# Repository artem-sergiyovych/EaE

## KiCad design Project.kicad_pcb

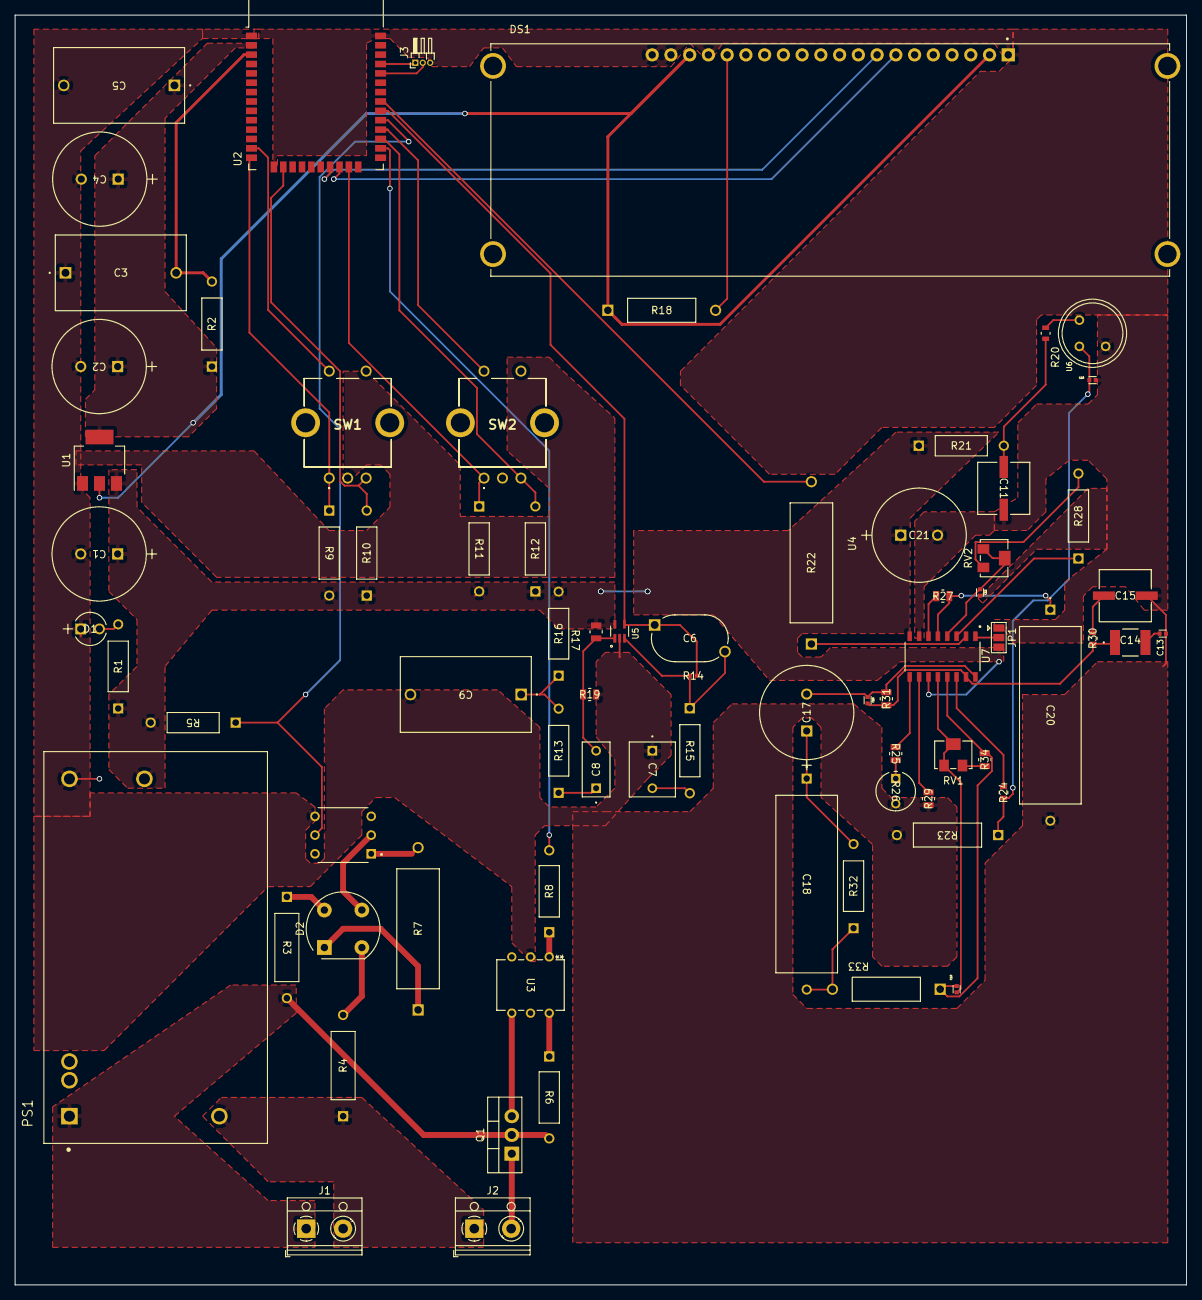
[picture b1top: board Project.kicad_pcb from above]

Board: 2 copper layers, 158.8 x 172.1 mm, 75 parts (0 on the bottom side), 59 nets.

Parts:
C1, C2, C4: 22uF; PCAP_125x25_PAN
C3, C5: 0.1uF; CAP_BFC233814104_VIS
C6: 100p; 564R60GAT10_VIS
C7: 1u; CAP_BFC237012105_VIS
C8: 0.01u; CAP_BFC237035223_VIS
C9: 0.1u; CAP_BFC233814104_VIS
C10, C12, C13, C16, C19: 103; CAPC1005X55N
C11, C15: 47u; CAP_EEFK_D_PAN
C14: 502; CAP_1812_AVX
C17, C21: 22u; PCAP_125x25_PAN
C18, C20: 104; WMF_08.1DX23.8LX0.6d_CND
D1: LED; LED_SSL-LX30_T-3_LUM
D2: W04G; Diode_Bridge_Round_D9.8mm
DS1: NHD-0420CW-AB3; LCD_NHD-0420CW-AB3
J1, J2: Screw_Terminal_01x02; TerminalBlock_RND_205-00012_1x02_P5.00mm_Horizontal
J3: Conn_01x03_Pin; PinHeader_1x03_P1.00mm_Horizontal
JP1: Jumper_3_Open; SolderJumper-3_P1.3mm_Open_Pad1.0x1.5mm
PS1: PSK-S25B-5-PB; CONV_PSK-S25B-5-PB
Q1: BT136-500; TO-220-3_Vertical
R1: 2K; RES_TYCO_YR1_TYC
R2, R5: 10K; RES_CFR25_TYCO_TYC
R3, R4: 47K; RES_CFR50_TYCO_TYC
R6, R8: 330; RES_LR1_TYCO_TYC
R7, R22: 1K; RES_CFR200_TYCO_TYC
R9, R10, R11, R12, R15, R21, R28: 10k; RES_CFR25_TYCO_TYC
R13, R16, R32: 2k; RES_TYCO_YR1_TYC
R14: 100k; RES0402_CRG_TYCO_TYC
R17, R19, R25, R27, R29, R31: 1M; RES0805_CRG_TYCO_TYC
R18, R33: 6.8k; RES_ROX1S_TYCO_TYC
R20, R24, R30: 18k; RES0603_CRG_TYCO_TYC
R23: 47k; RES_CFR50_TYCO_TYC
R26: R_Photo; LDR1_NTE
R34: 470k; RES0805_CRG_TYCO_TYC
RV1, RV2: 1M; Potentiometer_Bourns_3214W_Vertical
SW1, SW2: PEC11H; PEC11H4025FS0016
U1: AMS1117-3.3; SOT-223-3_TabPin2
U2: ESP32-WROOM-32; ESP32-WROOM-32D
U3: MOC3021M; PDIP6_BX_ONS
U4: MCT2E; DIP762W50P254L742H480Q6
U5: MAX4466EXK; SOT65P210X110-5N
U6: RE200B; SNR3-D8.1XH4.2MM
U7: BISS0001; SOIC127P600X180-16N

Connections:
AC230N: J1.2, J2.1, PS1.2 (AC(N)), R4.1
AC230P: J1.1, PS1.1 (AC(L)), Q1.2 (A2), R3.2, R6.2
ENC1_1: R10.2, SW1.B1, U2.16 (IO13)
ENC1_2: R9.1, SW1.A1, U2.14 (IO12)
ENC2_1: R12.2, SW2.B1, U2.27 (IO16)
ENC2_2: R11.1, SW2.A1, U2.23 (IO15)
GND: C1.2, C2.2, C3.1, C4.2, C5.2, C7.1, C9.2, C10.2, C11.2, C12.2, C13.2, C15.2, C20.2, C21.2, D1.1 (K), DS1.1 (VSS), DS1.17 (BS0), DS1.19 (BS2), DS1.20 (VSS), J3.3, JP1.1 (A), PS1.4 (-VO), R19.2, R23.2, R26.2, R29.1, U1.1 (GND), U2.1 (GND), U2.15 (GND), U2.38 (GND), U3.2, U4.4, U5.2 (GND), U6.3 (G), U7.7 (VSS)
I2CCP: DS1.7 (DB0/SCLK/SCL), U2.22 (SDI/SD1)
I2CDP: DS1.8 (DB1/SDI/SDAIN), U2.21 (SDO/SD0)
LOAD1_P: J2.2, Q1.1 (A1)
MIC: C6.1, R14.2, U2.30 (IO18), U5.4 (OUT)
unnamed: C7.2, R15.2
unnamed: C9.1, R13.2, R16.1
unnamed: C11.1, R20.1, R21.2
unnamed: C13.1, C14.2
unnamed: C15.1, R30.2
unnamed: C17.1, C18.1, R32.2
unnamed: C18.2, R32.1, R33.2
unnamed: D1.2 (A), R1.2
unnamed: D2.1 (+), R7.1
unnamed: D2.3 (-), U4.2
unnamed: D2.2, R4.2
unnamed: D2.4, R3.1
unnamed: DS1.16 (~RES), R18.2
unnamed: JP1.2 (C), U7.1 (A)
unnamed: C8.1, R13.1
unnamed: Q1.3 (G), U3.4
unnamed: R6.1, U3.6
unnamed: R7.2, U4.1
unnamed: R8.1, U3.1
unnamed: R25.2, R26.1
unnamed: R28.2, RV2.3
unnamed: R34.1, RV1.3
unnamed: C3.2, R2.2, U2.3 (EN)
unnamed: C8.2, R17.2, R19.1, U5.1 (IN+)
unnamed: C6.2, R14.1, R15.1, U5.3 (IN-)
unnamed: R20.2, U6.1 (D)
unnamed: C10.1, R23.1, R24.1, U6.2 (S)
unnamed: R24.2, U7.14 (1IN+)
unnamed: C14.1, C16.2, R30.1, R31.1, U7.15 (1IN-)
unnamed: C16.1, C17.2, R31.2, U7.16 (1OUT)
unnamed: C19.2, R33.1, R34.2, U7.13 (2IN-)
unnamed: C19.1, RV1.1, RV1.2, U7.12 (2OUT)
unnamed: R29.2, U7.10 (IB)
unnamed: C12.1, RV2.1, RV2.2, U7.4 (RC1)
unnamed: C20.1, R27.2, U7.5 (RC2)
unnamed: R28.1, U7.3 (RR1)
unnamed: R27.1, U7.6 (RR2)
unnamed: R25.1, U7.9 (VC)
unnamed: R22.1, U7.2 (VO)
PIR_SENS: R22.2, U2.31 (IO19)
SW1: SW1.S1, U2.13 (IO14)
SW2: SW2.S1, U2.28 (IO17)
TRIAC_1: R8.2, U2.26 (IO4)
UART_RX: J3.2, U2.34 (RXD0/IO3)
UART_TX: J3.1, U2.35 (TXD0/IO1)
VDD5: C1.1, C21.1, JP1.3 (B), PS1.3 (+VO), R1.1, R5.2, R9.2, R10.1, R11.2, R12.1, R16.2, R17.1, R21.1, U1.3 (VI), U5.5 (VCC), U7.8 (VRF/~RESET), U7.11 (VDD)
VDD33: C2.1, C4.1, C5.1, DS1.2 (VDD), DS1.18 (BS1), R2.1, R18.1, U1.2 (VO), U2.2 (VDD)
ZC: R5.1, U2.29 (IO5), U4.5

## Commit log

2023-12-19 Initial
2023-12-23 Add files via upload
    The start of work with a correct layout and principles of design
2023-12-30 Changed devboard to mcu
    -Changed devboard to standalone mcu
    -added 5v to 3.3v stabilizer
2023-12-30 AC dimmer
    Added AC dimmer and conectors
2024-01-09 Footprints, prices
    All available components got assigned with their footprints, price-list is updated
2024-01-10 Fixing the libraries linking
2024-01-10 Added 3d models
2024-01-10 Realocating of files
2024-01-13 Rotary encoders added
    Added 2 rotary encoders
2024-01-13 Added microphone
2024-01-13 Added PIR sensor
2024-01-13 Added footprints
    To-do finish list:
    *Add connection LED disp<->MCU
    *Assign footprints to:
    Capacitors: 10,12,13,14,16,18,19,20;
    Jumper JP1;
    Mikrophone MK1;
2024-01-13 Recommit
2024-01-16 models
    several 3d models were added
2024-01-18 capacitors
    capacitors footprints and resistor 3d models were added successfully
2024-01-22 UART and PCB Design rules
2024-01-23 LED
    LED was connected
2024-01-23 LED
    LED was added
2024-01-23 LED
    LED has been connected
2024-01-26 PCB components arranged + Power traces
2024-01-26 PCB finished
2024-01-26 Generated Gerber files
2024-01-26 3D models
2024-01-26 BOM file added
